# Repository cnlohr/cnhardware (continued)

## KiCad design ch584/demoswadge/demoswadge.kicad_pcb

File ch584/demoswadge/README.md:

# cnlohr's ideal mini swadge

## Goals
 * Swadges have lost their novelty because they're all the same
 * Swadges are too heavy and big.  Smaller. Lighter.
 * Swadges are expensive, what if we make them much cheaper? Can we make more?
 * Keep as much connectivity/features as are visible.  We have to pick and choose.
   * USB ($0.05)
   * Buttons ($0.10)
   * Audio Out ($0.14)
   * Audio In ($0.18)
   * LEDs ($0.35)
   * IMU ($0.55)
   * Compatibility with ESP32-S2 wireless ($1.80)
   * Display ($1.20)
   * Color Display ($2.80)
 * Needs to be more enclosed.

## Spec

 * Single AA Battery, BH-AA-A1AJ020
 * CPU: CH584M (C42381470)
   * 78MHz, RISC-V, IMBC
   * 504kB Flash (Optional +512kB in CH584X)
   * 96kB RAM
   * 2.4GHz (BLE-only, no wifi) support
   * NFC (13.56 MHz RFID)
   * USBFS (Could be USBHS if 585M)
   * 40 GPIOs
   * Processor current is:
     * 5uA Standby (with RTC)
     * 2mA Operating, no radio
     * 7mA (RX)
     * 12mA (Peak TX)
 * Boost supply
   * C5345596, 2.2V VDD, CH584 can run at low voltage.
   * LDO for USB operation to 3.3VDD.
 * OLED or LCD
   * Consider OLED because lower power
   * Consider monochrome OLED for cost (Could 2bit greyscale)
   * Consider LCD but higher power, for color.
 * Silicone Buttons	
 * LEDs (Recommend no LEDs) LC8805C
 * SMALLER PCB (Recommend 35x60)
 * Add a case (not quoted) or triple-stack PCB
 * Recommend no speaker, but headphone jack. Digital volume control.
 * Consider soft-power-switch-only to enable RTC
 * USB (For programmability or other features)

### Costs (@1000)

| Component | Cost | Energy (Active, 100% RX) |
| --- | --- | --- |
| CPU | $0.56 | 7mA |
| Boost x2, LDO | $0.11 | 10-20uA |
| Battery Holder | $0.22 | - |
| LCD/OLED | $2.00-$3.00 | 9-100mA |
| Silicone Buttons | $0.06-$0.35 | - |
| PCB | $0.21-$0.63 | - |
| Misc Discretes | $0.15 | - |
| USB (SOUHAN connector) | $0.05 | - |
| Mic (GMI4013S-2C56DB) | $0.14 | - |
| Headphones PJ-307C | $0.04 | - |
| Crystals (assume internal RTC) | $0.04 | - |
| --- | Optional | --- |
| LEDs 4x | $0.18 | 2mA to 62mA |
| LSM6DS3TR | $0.66 | 450uA (Active mode) |

Silicone button candidates:
 * 
 * 
 * DonGuan Deson Insulated MAterial Co., LTD 10x6x9 Clear, 30k, $0.017/ea

LEDs:
 * LC8805C

PCB:
 * Assumes PCBWay, 35x60, 2L, Lead-free HASL
 * If no case, need 2 extra PCBs to sandwich buttons and OLED/LCD panel.

## Software Recommendations

 * Recommend CH32FUN
 * Recommend compressed loading for game mode.
 * Common funcitons remain in FLASH.
 * Each game has 100% of RAM to itself.
 * Assets **may** stay in FLASH or be loaded into RAM.

## Avenues
 * ESP32-S3 + new screen // AND // Microswadge
 * Micro-swadge only with LCD?

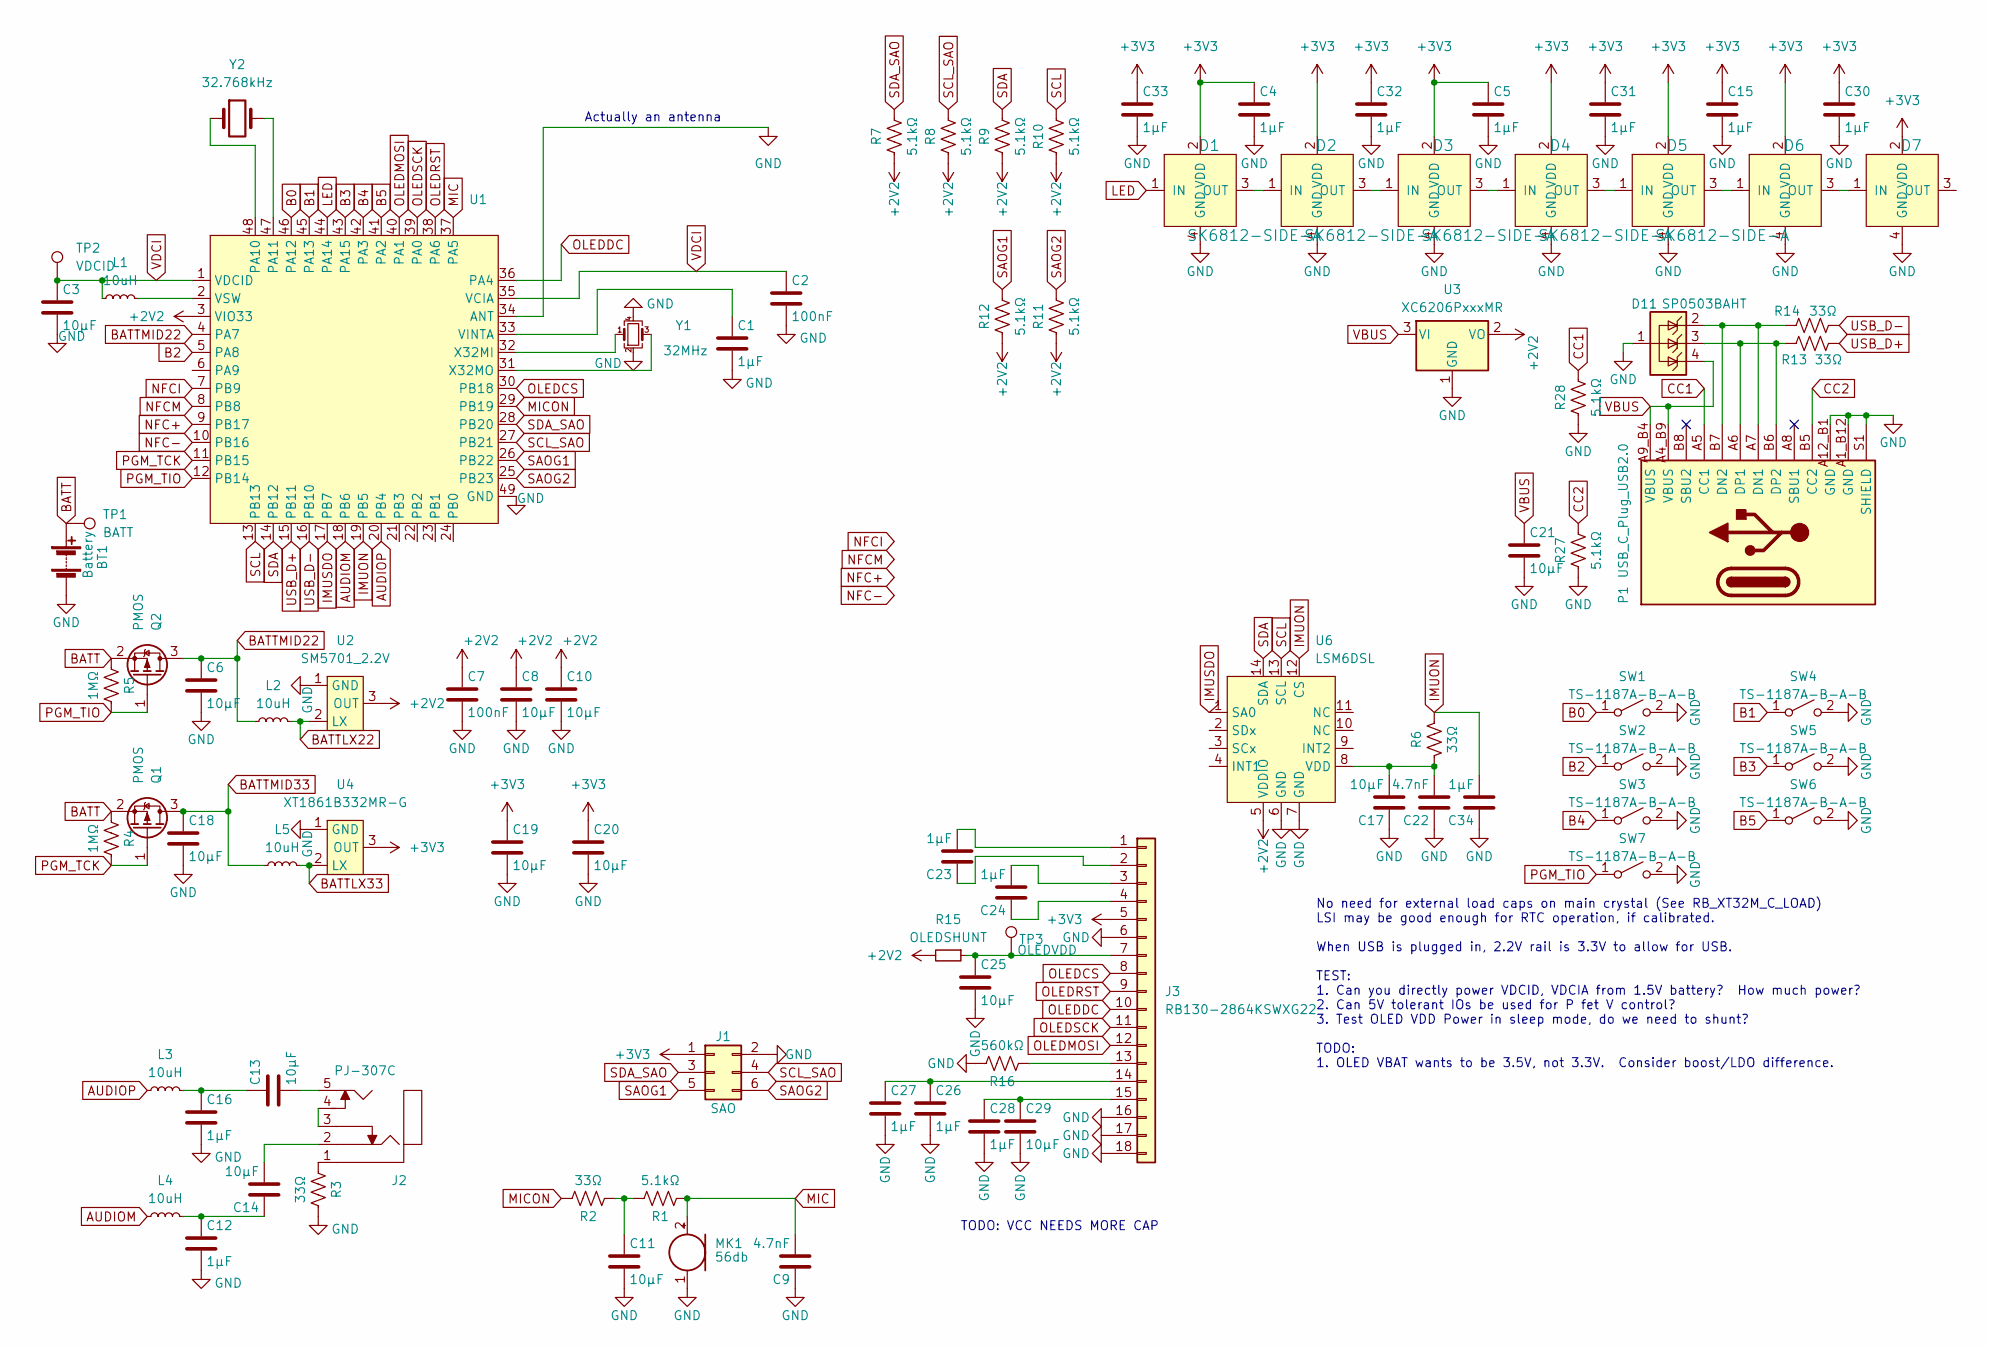
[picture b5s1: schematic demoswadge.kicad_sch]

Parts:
BT1: Battery; 2460; Digikey 36-2460-ND
C1, C4, C5, C12, C15, C16, C23, C24, C26, C27, C28, C30, C31, C32, C33, C34: 1μF; C_0402_1005Metric; LCSC C52923
C2, C7: 100nF; C_0402_1005Metric; LCSC C1525
C3, C6, C8, C10, C11, C13, C14, C17, C18, C19, C20, C21, C25, C29: 10μF; C_0603_1608Metric; LCSC C19702
C9, C22: 4.7nF; R_0402_1005Metric_COMPACT; LCSC C1538
D1, D2, D3, D4, D5, D6, D7: SK6812-SIDE-A; SK6812_SIDE_2; Digikey 1528-4691-ND
D11: SP0503BAHT; SOT-143; Digikey F2715CT-ND
J1: SAO; PinHeader_2x03_P2.54mm_Vertical; LCSC C92272
J2: PJ-307C; LCSC C16684
J3: RB130-2864KSWXG22; FPC-16-P0.50mm-HC-FPC-05-09-16RLTAG-TOP-AND-BOTTOM; LCSC C5213753
L1, L2, L3, L4, L5: 10uH; L_0603_1608Metric; LCSC C307750
MK1: 56db; INGHAi_MIC_GMI4013S-2C58DB; LCSC C529869
P1: USB_C_Plug_USB2.0; USB_C_Receptacle_HRO_TYPE-C-31-M-12; LCSC C2765186
Q1, Q2: PMOS; SOT-23; LCSC C10487
R1, R7, R8, R9, R10, R11, R12, R27, R28: 5.1kΩ; R_0402_1005Metric_COMPACT; LCSC C25905
R2, R3, R6, R13, R14: 33Ω; R_0402_1005Metric_COMPACT; LCSC C25105
R4, R5: 1MΩ; R_0402_1005Metric_COMPACT; LCSC C26083
R15: OLEDSHUNT; R_0402_1005Metric_COMPACT
R16: 560kΩ; R_0402_1005Metric_COMPACT; LCSC C132339
SW1, SW2, SW3, SW4, SW5, SW6, SW7: TS-1187A-B-A-B; BTC007_Button_Silicone
TP1: BATT; TestPoint_Pad_D1.0mm
TP2: VDCID; TestPoint_Pad_D1.0mm
TP3: OLEDVDD; TestPoint_Pad_D1.0mm
U1: QFN-48-1EP_5x5mm_P0.35mm_EP3.7x3.7mm; LCSC C42381470
U2: SM5701_2.2V; SOT-23; LCSC C5345596
U3: XC6206PxxxMR; SOT-23-3; LCSC C5446
U4: XT1861B332MR-G; SOT-23; LCSC C236396
U6: LSM6DSL; LGA-14_3x2.5mm_P0.5mm_LayoutBorder3x4y; LCSC C967633
Y1: 32MHz; Crystal_SMD_2016-4Pin_2.0x1.6mm; LCSC C2965584
Y2: 32.768kHz; Crystal_SMD_3215-2Pin_3.2x1.5mm; LCSC C7294751

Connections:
+2V2: C7.1, C8.1, C10.1, R7.1, R8.1, R9.1, R10.1, R11.1, R12.1, R15.2, U1.3 (VIO33), U2.3 (OUT), U3.2 (VO), U6.5 (VDDIO)
+3V3: C4.1, C5.1, C15.1, C19.1, C20.1, C30.1, C31.1, C32.1, C33.1, D1.2 (VDD), D2.2 (VDD), D3.2 (VDD), D4.2 (VDD), D5.2 (VDD), D6.2 (VDD), D7.2 (VDD), J1.1, J3.5, U4.3 (OUT); also elsewhere on the board
AUDIOM: L4.1, U1.18 (PB6)
AUDIOP: L3.1, U1.20 (PB4)
B0: SW1.1 (A), U1.46 (PA12)
B1: SW4.1 (A), U1.45 (PA13)
B2: SW2.1 (A), U1.5 (PA8)
B3: SW5.1 (A), U1.43 (PA15)
B4: SW3.1 (A), U1.42 (PA3)
B5: SW6.1 (A), U1.41 (PA2)
BATT: BT1.1 (+), Q1.2 (S), Q2.2 (S), R4.1, R5.1, TP1.1
BATTLX22: L2.2, U2.2 (LX)
BATTLX33: L5.2, U4.2 (LX)
BATTMID22: C6.1, L2.1, Q2.3 (D), U1.4 (PA7)
BATTMID33: C18.1, L5.1, Q1.3 (D)
CC1: P1.A5 (CC1), R28.2
CC2: P1.B5 (CC2), R27.2
GND: BT1.2 (-), C1.2, C2.2, C3.2, C4.2, C5.2, C6.2, C7.2, C8.2, C9.1, C10.2, C11.2, C12.2, C15.2, C16.2, C17.1, C18.2, C19.2, C20.2, C21.2, C22.1, C25.2, C26.2, C27.2, C28.2, C29.2, C30.2, C31.2, C32.2, C33.2, C34.1, D1.4 (GND), D2.4 (GND), D3.4 (GND), D4.4 (GND), D5.4 (GND), D6.4 (GND), D7.4 (GND), D11.1 (A), J1.2, J3.6, J3.16, J3.17, J3.18, MK1.1 (-), P1.A1_B12 (GND), P1.A12_B1 (GND), P1.S1 (SHIELD), R3.2, R16.2, R27.1, R28.1, SW1.2 (B), SW2.2 (B), SW3.2 (B), SW4.2 (B), SW5.2 (B), SW6.2 (B), SW7.2 (B), U1.34 (ANT), U1.49 (GND), U2.1 (GND), U3.1 (GND), U4.1 (GND), U6.6 (GND), U6.7 (GND), Y1.2, Y1.4; also elsewhere on the board
IMUON: C34.2, R6.1, U1.19 (PB5), U6.12 (CS)
IMUSDO: U1.17 (PB7), U6.1 (SA0)
LED: D1.1 (IN), U1.44 (PA14)
MIC: C9.2, MK1.2 (+), R1.1, U1.37 (PA5)
MICON: R2.2, U1.29 (PB19)
NFC+: U1.9 (PB17)
NFC-: U1.10 (PB16)
NFCI: U1.7 (PB9)
NFCM: U1.8 (PB8)
unnamed: C11.1, R1.2, R2.1
unnamed: C12.1, C14.1, L4.2
unnamed: C13.1, C16.1, L3.2
unnamed: C13.2, J2.5
unnamed: C14.2, J2.2
unnamed: D1.3 (OUT), D2.1 (IN)
unnamed: D2.3 (OUT), D3.1 (IN)
unnamed: D3.3 (OUT), D4.1 (IN)
unnamed: D4.3 (OUT), D5.1 (IN)
unnamed: D5.3 (OUT), D6.1 (IN)
unnamed: D6.3 (OUT), D7.1 (IN)
unnamed: J2.1, R3.1
unnamed: J2.3, J2.4
unnamed: C23.2, J3.1
unnamed: C23.1, J3.2
unnamed: C24.2, J3.3
unnamed: C24.1, J3.4
unnamed: C25.1, J3.7, R15.1, TP3.1
unnamed: J3.13, R16.1
unnamed: C26.1, C27.1, J3.14
unnamed: C28.1, C29.1, J3.15
unnamed: D11.2 (K), P1.A7 (DN1), P1.B7 (DN2), R14.2
unnamed: D11.3 (K), P1.A6 (DP1), P1.B6 (DP2), R13.2
unnamed: U1.48 (PA10), Y2.1
unnamed: U1.47 (PA11), Y2.2
unnamed: C1.1, U1.33 (VINTA)
unnamed: L1.2, U1.2 (VSW)
unnamed: U1.32 (X32MI), Y1.1
unnamed: U1.31 (X32MO), Y1.3
unnamed: C17.2, C22.2, R6.2, U6.8 (VDD)
OLEDCS: J3.8, U1.30 (PB18)
OLEDDC: J3.10, U1.36 (PA4)
OLEDMOSI: J3.12, U1.40 (PA1)
OLEDRST: J3.9, U1.38 (PA6)
OLEDSCK: J3.11, U1.39 (PA0)
PGM_TCK: Q1.1 (G), R4.2, U1.11 (PB15)
PGM_TIO: Q2.1 (G), R5.2, SW7.1 (A), U1.12 (PB14)
SAOG1: J1.5, R12.2, U1.26 (PB22)
SAOG2: J1.6, R11.2, U1.25 (PB23)
SCL: R10.2, U1.13 (PB13), U6.13 (SCL)
SCL_SAO: J1.4, R8.2, U1.27 (PB21)
SDA: R9.2, U1.14 (PB12), U6.14 (SDA)
SDA_SAO: J1.3, R7.2, U1.28 (PB20)
USB_D+: R13.1, U1.15 (PB11)
USB_D-: R14.1, U1.16 (PB10)
VBUS: C21.1, D11.4 (K), P1.A4_B9 (VBUS), P1.A9_B4 (VBUS), U3.3 (VI)
VDCI: C2.1, C3.1, L1.1, TP2.1, U1.1 (VDCID), U1.35 (VCIA)

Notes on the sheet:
TODO: VCC NEEDS MORE CAP
No need for external load caps on main crystal (See RB_XT32M_C_LOAD) LSI may be good enough for RTC operation, if calibrated. When USB is plugged in, 2.2V rail is 3.3V to allow for USB. TEST: 1. Can you directly power VDCID, VDCIA from 1.5V battery? How much power? 2. Can 5V tolerant IOs be used fo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
Actually an antenna

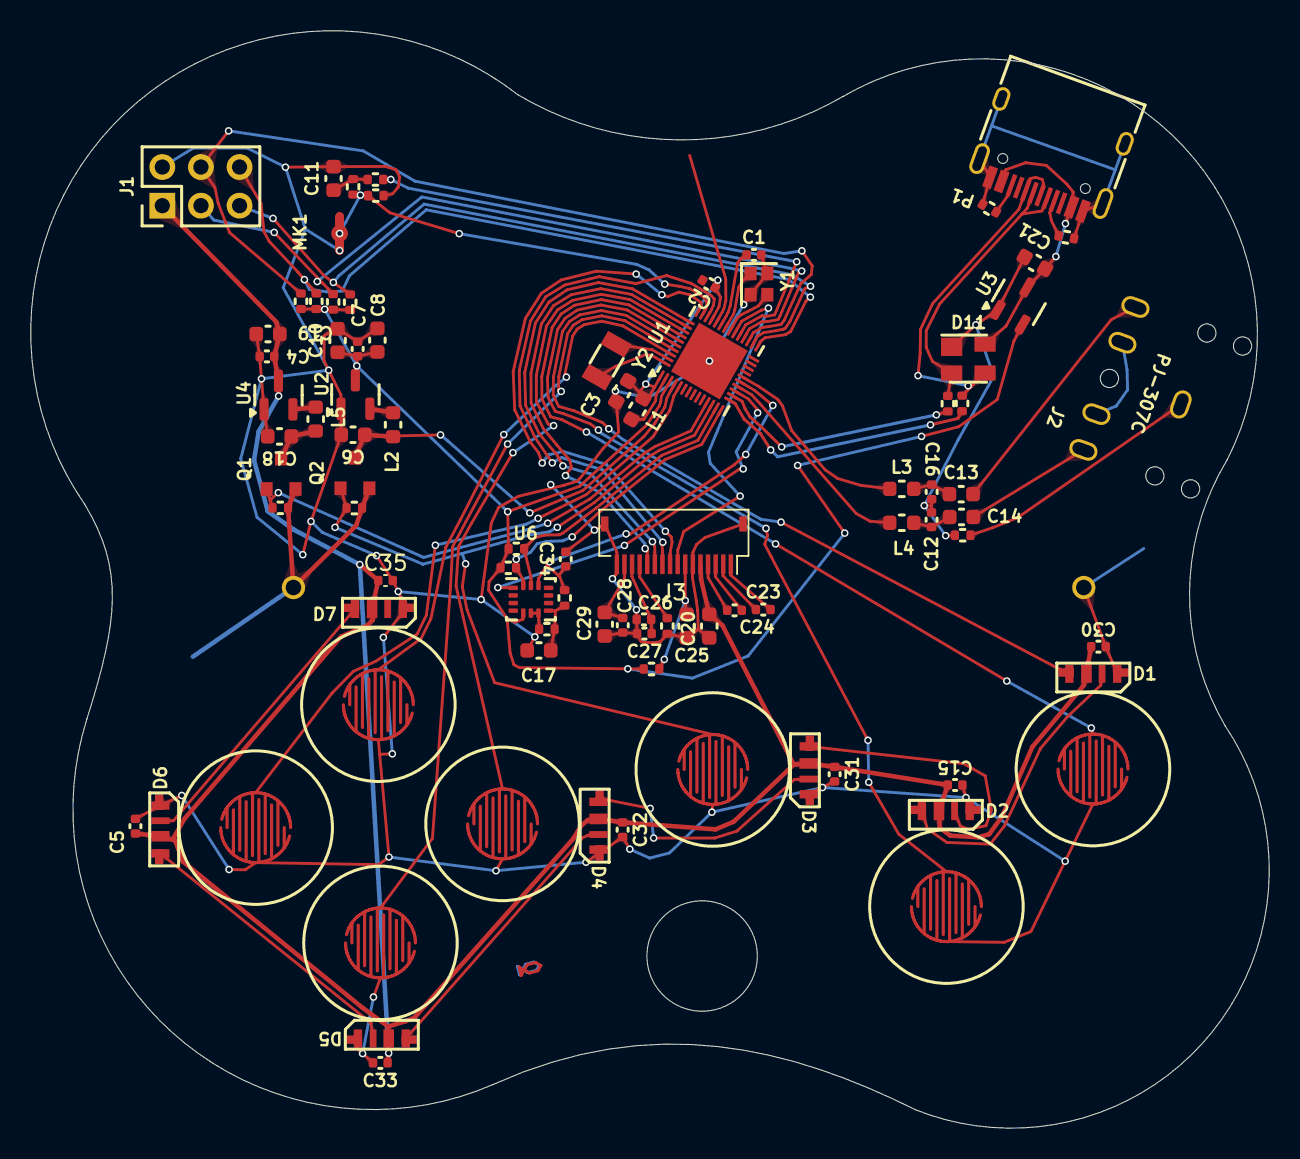
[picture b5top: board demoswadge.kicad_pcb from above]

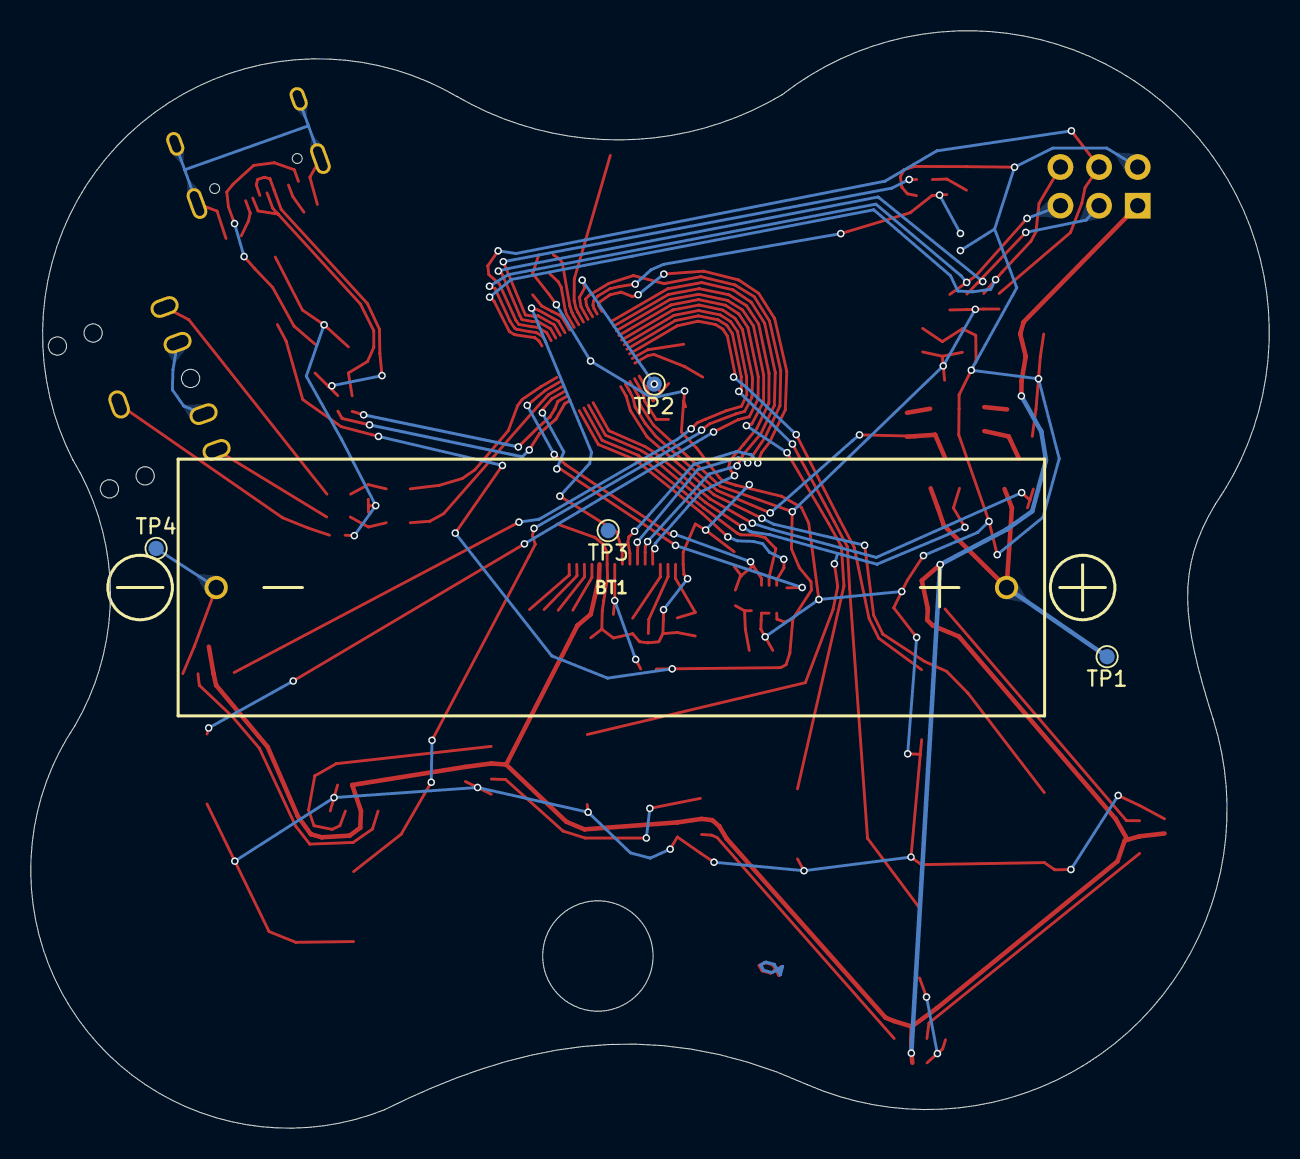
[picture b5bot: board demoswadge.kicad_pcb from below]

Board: 2 copper layers, 81.5 x 72.2 mm, 92 parts (5 on the bottom side), 70 nets.

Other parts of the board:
C35: 1μF; C_0402_1005Metric
TP4: GND; TestPoint_Pad_D1.0mm

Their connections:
+3V3: C35.1; also elsewhere on the board
GND: C35.2, TP4.1; also elsewhere on the board

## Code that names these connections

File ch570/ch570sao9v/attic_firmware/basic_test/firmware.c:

/* Small example showing how to use the SWIO programming pin to 
   do printf through the debug interface */

#include "ch32fun.h"
#include <stdio.h>

#define SH1107_128x128

#define SSD1306_RST_PIN  PA6
#define SSD1306_CS_PIN   PA4
#define SSD1306_DC_PIN   PA10
#define SSD1306_MOSI_PIN PA7
#define SSD1306_SCK_PIN  PA5

//#define SSD1306_SOFT_SPI 1

#include "ssd1306_spi.h"
#include "ssd1306.h"

uint32_t count;





/////////////////////////////////////////////////////////////////////////////////////////////////
/////////////////////////////////////////////////////////////////////////////////////////////////
// FakeDC
//
// Fake digital-to-analog, by looking at the time constant on a capcaitor
// and waiting for the scmitt trigger flip.
//

#define CAPACITANCE 0.00000001
#define RESISTANCE  33000.0
#define VREF 1.75
#define FIXEDPOINT_SCALE 100

volatile uint32_t lastfifo = 0;

void TMR1_IRQHandler(void) __attribute__((interrupt))  __attribute__((section(".srodata")));
void TMR1_IRQHandler(void)
{
	R8_TMR_INT_FLAG = 2;
	lastfifo = R32_TMR_FIFO;
	funPinMode( PA2, GPIO_ModeOut_PP_20mA );
}


// The timing on the setup has to be tight.
void EventRelease(void) __attribute__((section(".srodata"))) __attribute__((noinline));
void EventRelease(void)
{
	R8_TMR_CTRL_MOD = 0b00000010; // Reset Timer
	R8_TMR_CTRL_MOD = 0b11000101; // Capture mode rising edge
	funPinMode( PA2, GPIO_ModeIN_Floating );
}

void SetupADC(void)
{
	R8_TMR_CTRL_MOD = 0b00000010; // All clear
	R32_TMR_CNT_END = 0x03FFFFFF; // Maximum possible counter size.
	R8_TMR_CTRL_MOD = 0b11000101; // Capture mode rising edge
	R8_TMR_INTER_EN = 0b10; // Capture event.

	R16_PIN_ALTERNATE_H |= 1<<6; // Map PA2 to CAP1 (could be PA7, PA4, or PA9) (see RB_TMR_PIN)

	NVIC_EnableIRQ(TMR1_IRQn);
	__enable_irq();

	funPinMode( PA2, GPIO_ModeOut_PP_20mA );
}

/////////////////////////////////////////////////////////////////////////////////////////////////















int main()
{
	SystemInit();

	funGpioInitAll(); // no-op on ch5xx

	funPinMode( PA11, GPIO_CFGLR_OUT_10Mhz_PP );
//	funDigitalWrite( PA11, 1 ); // BS1 = 1 for I2C
	funDigitalWrite( PA11, 0 ); // BS1 = 0 for SPI

	funPinMode( PA6, GPIO_CFGLR_OUT_10Mhz_PP );
	funDigitalWrite( PA6, 1 ); // RES
	funPinMode( PA4, GPIO_CFGLR_OUT_10Mhz_PP );
	funDigitalWrite( PA4, 0 ); // SCS
	funPinMode( PA10, GPIO_CFGLR_OUT_10Mhz_PP );
	funDigitalWrite( PA10, 0 ); // D/C



	ssd1306_rst();
	ssd1306_spi_init();
	ssd1306_init();
	ssd1306_setbuf(0x00);

	// Turbo-time
	ssd1306_cmd(0xD5);
	ssd1306_cmd(0xe0);


	ssd1306_cmd(0xc8);
	ssd1306_cmd(0xa1);


	SetupADC();

	int frameno = 0;

	int debug = 0;

	unsigned start;

	while(1)
	{

		start = SysTick->CNT;

		uint32_t pressures[4];

		int btn = 0;
		for( btn = 0; btn < 4; btn++ )
		{
			// try GPIO_CFGLR_IN_PUPD, GPIO_ModeIN_Floating, GPIO_CFGLR_OUT_10Mhz_PP as well
			funPinMode( PA3, GPIO_ModeIN_Floating );
			funPinMode( PA8, GPIO_ModeIN_Floating );
			funPinMode( PA9, GPIO_ModeIN_Floating );
			switch( btn )
			{
			case 0:
				funPinMode( PA8, GPIO_CFGLR_OUT_10Mhz_PP );
				funDigitalWrite( PA3, 1 );
				break;
			case 1:
				funPinMode( PA9, GPIO_CFGLR_OUT_10Mhz_PP );
				funDigitalWrite( PA8, 1 );
				break;
			case 2:
				funPinMode( PA3, GPIO_CFGLR_OUT_10Mhz_PP );
				funDigitalWrite( PA9, 1 );
				break;
			}


			lastfifo = 0;
			EventRelease();
			int to = 4000;
			while( !lastfifo && --to );

			#define COEFFICIENT (const uint32_t)(FUNCONF_SYSTEM_CORE_CLOCK*(RESISTANCE*CAPACITANCE)*VREF*FIXEDPOINT_SCALE+0.5)
			int r = lastfifo - 2; // 2 cycles back.
			int vtot = COEFFICIENT/r + ((const uint32_t)(VREF*FIXEDPOINT_SCALE));
			pressures[btn] = vtot - 70;
		}
		debug = SysTick->CNT - start;
		frameno++;
		
		ssd1306_setbuf(0x00);

		char st[128];
		sprintf( st, "%08x", (int)SysTick->CNT );
		ssd1306_drawstr_sz(0, 0, st, 1, 2 );

		sprintf( st, "%3d %d", debug>>8, (int)pressures[3] );
		ssd1306_drawstr_sz(0, 24, st, 1, 2 );


		for( btn = 0; btn < 3; btn++ )
		{
			int x = 32 + btn * 32;
			int y = 90;
			int p = pressures[btn]>>9;
			//ssd1306_drawCircle( x, y, 
			ssd1306_fillCircle( x, y, p, 1 );
		}


		ssd1306_refresh();
	}
}

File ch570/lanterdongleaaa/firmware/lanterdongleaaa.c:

/* 
	In progress.  Trying to jank an ADC out of a ch57x.

	// Mic (with pull-up) on pa3
	// RC on PC7->PC2
*/


#include "ch32fun.h"
#include <stdio.h>

#include "ch5xx_lowpower.h"
#include "color_utilities.h"

#ifdef CH570_CH572
#define LED PA9
#else
#define LED PA8
#endif


#define USE_UART_OUT

uint32_t count;
int initialSWD;
int frameno = 18;

int last = 0;
void handle_debug_input( int numbytes, uint8_t * data )
{
	last = data[0];
	count += numbytes;
}

uint32_t timer_data[256];


void RunFunction() __HIGH_CODE;

void OutputLEDs( uint32_t * ledcolors )
{
	int led;
	for( led = 0; led < 6; led++ )
	{
		uint32_t color = ledcolors[led];
		for( int cb = 0; cb < 24; cb += 1 )
		{
			// USART is - I think? LSB first?
			// LOW (start) / x x H L x x H H H(stop?)
			uint8_t pair = ((color >> (23-cb))&1);
			//const uint8_t sendc[4] = { 0b00001000, 0b00001111, 0b11101000, 0b11101111, };
			//const uint8_t sendc[2] = { 0b10000000, 0b11111110 };
			//while(!(R8_UART1_LSR & RB_LSR_TX_ALL_EMP));
			//Delay_Us(1);
			if( pair )
			{
				funDigitalWrite( PA1, 1 );
				ADD_N_NOPS(40);
				funDigitalWrite( PA1, 0 );
				ADD_N_NOPS(12);
			}
			else
			{
				funDigitalWrite( PA1, 1 );
				ADD_N_NOPS(12);
				funDigitalWrite( PA1, 0 );
				ADD_N_NOPS(40);
			}
			//R8_UART1_THR = sendc[pair];
		}
	}
}

#define PWMCLOCKDIV 4
#define INITIAL_ZERO 128
// SPS = F_CPU/(PWMCLOCKDIV*255*oversample)

// Highest quality combination so far - 100MHz / (1 oversample*5clockdiv*255) = 78.431kSPS
// Good quality combination so far - 75MHz / (1 oversample*5clockdiv*255) = 78.824kSPS
// Actually amazing: 100MHz / (1 oversample*4clockdiv*255) = 98.039kSPS

void RunFunction()
{

	const uint32_t oversample = 4;
	const uint32_t targetsampletime = oversample*(255*R16_PWM_CLOCK_DIV); // in 1/60Mths of a second.

	uint32_t * rptr = timer_data;
	uint32_t * end = &timer_data[sizeof(timer_data)/sizeof(timer_data[0])];
	uint32_t place = 0;
	int32_t rvalue = 0;

	int remote_estimate = 0;

	int accumulated_dc = 0;

	LSIEnable(); // Disable LSE, enable LSI
	RTC_init();

	// LED Test
#if 0
	R16_PIN_ALTERNATE &= ~RB_PIN_DEBUG_EN;

	//while(1)
	int i;
	for( i = 0; i < 10; i++ )
	{
		#define NR_LEDS 6
		static uint32_t ledcolors[NR_LEDS] = { 0x00ff00, 0x0000ff, 0x00ff00, 0x00ff00, 0xff00ff, 0x00ffff };

		static uint16_t phases[NR_LEDS];


		for( int k = 0; k < NR_LEDS; k++ )
		{
			phases[k] += ((((rands[k&0xff])+0xf)<<2) + (((rands[k&0xff])+0xf)<<1))>>1;
		}


		funDigitalWrite( PA1, 0 );
		funPinMode(PA1, GPIO_CFGLR_IN_PUPD );
		Delay_Ms(3);
		funPinMode(PA1, GPIO_CFGLR_OUT_50Mhz_PP); //LED Out / Buttons in
		Delay_Us(50);

		volatile int tween = -NR_LEDS;

		int ledno;
		for( ledno = 0; ledno < NR_LEDS; ledno++ )
		{
			uint8_t index = (phases[ledno])>>8;
			uint8_t rsbase = sintable[index];
			uint8_t rs = rsbase>>3;
			uint32_t fire = ((huetable[(rs+190)&0xff]>>1)<<0) | ((huetable[(rs+30)&0xff])<<8) | ((huetable[(rs+0)]>>1)<<16);

			uint32_t rgbuke  = ((huetable[(frameno+170+ledno*40)&0xff]>>1)<<0) | ((huetable[(frameno+85+ledno*40)&0xff]>>1)<<8) | ((huetable[(frameno+0+ledno*40)&0xff]>>1)<<16);

			// Because this chip doesn't natively support multiplies, we are going to avoid tweening of 1..254.
			//return TweenHexColors( fire, ice, ((tween + ledno)>0)?255:0 ); // Where "tween" is a value from 0 ... 255
			ledcolors[ledno] = rgbuke;

		}

		OutputLEDs(ledcolors);

		int i;
		for( i = 0; i < 8; i++ )
		{
			Delay_Ms(1);
			//LowPowerIdle( MS_TO_RTC(1) );
			//DCDCEnable(); // During low power mode, the DCDC is disabled so we need to enable it

			if( initialSWD != funDigitalRead( PA0 ) )
			{
				R16_PIN_ALTERNATE |= RB_PIN_DEBUG_EN;
			}
		}
		frameno++;
	}
	R16_PIN_ALTERNATE |= RB_PIN_DEBUG_EN;

#endif

	while(1)
	{
		uint32_t * cnow = (void*) (R16_TMR_DMA_NOW | (((intptr_t)timer_data)&0xffff0000));
		if( cnow == end ) cnow = end - 1;
		while( rptr != cnow )
		{
			uint32_t v = *(rptr++);

			// For each edge.
			int negative = 0;
			if( v & 0x02000000 )
			{
				v = v & 0x1ffffff;
				negative = 1;
			}

			int tprog = v;

//			place += v;

			do
			{
				int leftover = place + tprog - targetsampletime;

				if( leftover > 0 )
				{
					// We bridge over.  Need to see how much data was left.
					int fillcur = targetsampletime - place;
					place += fillcur;
					tprog -= fillcur;
					if( negative )
						rvalue -= fillcur;
					else
						rvalue += fillcur;					
				}
				else
				{
					// No leftover.  Add remaining part.
					place += tprog;
					if( negative )
						rvalue -= tprog;
					else
						rvalue += tprog;
					break;
				}

//rvalue is always divisible by 2.
rvalue>>=1;

static int ifp, rvmin, rvmax;
ifp++;

if( ifp == 1000 )
{
	printf( "%d %d %d\n", rvalue, R8_PWM1_DATA, rvmax-rvmin );
	//printf( "." );
	rvmin = 100000;
	rvmax = -100000;
	ifp = 0;
}
else
{
	if( rvalue < rvmin ) rvmin = rvalue;
	if( rvalue > rvmax ) rvmax = rvalue;
}

				//audio_samples[audiosamphead] = rvalue;
				//audiosamphead = (audiosamphead + 1) % ASAMPS;
#if 0
				int err = (rvalue>>2) - remote_estimate;
				int value = 0;

				if( err > 127 ) err = 127;
				if( err < -127 ) err = -127;
				value = err;

#if 0
	static int ak;
				ak++;
				value = ak;
#endif
				printf( "%d\n", value );
				remote_estimate += err;

#endif


				accumulated_dc += rvalue;
				rvalue = 0;

				place -= targetsampletime;
			} while(1);



			if( rptr == end ) rptr = timer_data;
		}


		//printf( "%08x\n", R16_TMR_DMA_NOW );
		// Should print 00001310 020000a0 00001310 020000a0
//		printf( "%08x %08x %08x %08x @ %08x\n", (int)timer_data[0], (int)timer_data[1], (int)timer_data[2], (int)timer_data[3], R16_TMR_DMA_NOW );
		//printf( "%6d %5d %d\n", audio_samples[audiosamphead], place, audiosamphead );
	//	printf( "%x\n",  audio_samples[(audiosamphead-1+ASAMPS)&(ASAMPS-1)]+32767 );
		//printf( "." );
	//	_write( 0, "12345", 5 );




		// Steps disrupt the sampling. Minimize how often we do it.
		if( accumulated_dc > 10000000 && R8_PWM1_DATA > 0 ) { R8_PWM1_DATA++; accumulated_dc = 0; }
		if( accumulated_dc <-10000000 && R8_PWM1_DATA < 254 ) { R8_PWM1_DATA--; accumulated_dc = 0; }
		accumulated_dc = accumulated_dc - (accumulated_dc>>23);

		//if( R8_PWM1_DATA++ > 28 ) R8_PWM1_DATA = 1;
	}
}

int main()
{
	SystemInit();

	funGpioInitAll(); // no-op on ch5xx

	// Pull-up PA3
//	R32_PA_PU |= 0b1100; // Extra pull-up on mic - why?
//	R32_PA_PD_DRV |= 0b0100;
	// doesn't do anything?

	// UART Config
//	SetupUART(FUNCONF_UART_PRINTF_BAUD); // UART1 on rx,tx:PA8,PA9 at 115200 baud (PA2,PA3 on ch570/2)

	//Not using UART: TXD_7: TXD pin mapping of UART.
	funPinMode(PA1, GPIO_CFGLR_OUT_50Mhz_PP); //LED Out

	funPinMode(PA7, GPIO_CFGLR_OUT_2Mhz_PP); //PWM1

	// Comparator mapping default.
	funPinMode(PA2, GPIO_CFGLR_IN_FLOAT); // PA2 is Microphone
	funPinMode(PA3, GPIO_CFGLR_IN_FLOAT); // PA3 is Sawtooth in.

	// Slight pull SWIO high.
	funDigitalWrite(PA0, 1); 
	funPinMode(PA0, GPIO_CFGLR_IN_PUPD ); 

	// TODO: Explore this. TODO Explore.
	SYS_SAFE_ACCESS(
		R16_AUX_POWER_ADJ = 1;
		R16_POWER_PLAN = RB_PWR_PLAN_EN | RB_PWR_SYS_EN | RB_PWR_RAM2K | RB_PWR_CORE;
	);

	SYS_SAFE_ACCESS(
		R16_POWER_PLAN |= RB_PWR_DCDC_EN; // Enable core DC DC
	);

	Delay_Ms(100);

	SYS_SAFE_ACCESS( 
		R16_PIN_ALTERNATE = 
			RB_PIN_DEBUG_EN | // Disable to disable debug.
			0b111101111100; // Low power unused pins.
		R16_PIN_ALTERNATE_H = 0; // All default mapping.
	);

	initialSWD = funDigitalRead( PA0 );

	// Configure comparator to output to timer capture.
	R32_CMP_CTRL = 
		(0<<25) | // RB_APR_OUT_CMP = realtime output. -- what does this even do?
		(0) |     // RB_CMP_SW = 0 = PA2/PA3.
		(1<<1) |  // RB_CMP_CAP = 1: Input comes from the comparator;
		(1<<0);   // RB_CMP_EN = 1.

	// Setup 26-bit capture timer - default on PA7.
	R8_TMR_CTRL_MOD = 
		(0b01<<6) | // RB_TMR_CAP_EDGE = Capture the time between any edge changes;
		0 |         // RB_TMR_CAP_COUNT = Capture mode.
		(1<<2) | 	// RB_TMR_COUNT_EN = 1
		(1<<1) |	// RB_TMR_ALL_CLEAR = 1
		(1<<0); 	// RB_TMR_MODE_IN = 1 (Input mode)
	R8_TMR_CTRL_MOD &= ~(1<<1); // Clear R8_TMR_CTRL_MOD.
	R16_TMR_DMA_BEG = (uintptr_t)&timer_data[0];
	R16_TMR_DMA_END = (uintptr_t)&timer_data[sizeof(timer_data)/sizeof(timer_data[0])]; // END is not inclusive.

	R8_TMR_CTRL_DMA =
		(1<<2) | // RB_TMR_DMA_LOOP
		(1<<0);  // RB_TMR_DMA_ENABLE


	// Base is 952.4 @ 5-bit (31 period) = 60MHz base clock.
	// Or 100MHz...
	R16_PWM_CLOCK_DIV = PWMCLOCKDIV;
    R8_PWM_OUT_EN |= (1 << (0)); // Enable output 0.
    R8_PWM_CONFIG &= ~(RB_PWM_CYC_MOD | RB_PWM_CYCLE_SEL);
    R8_PWM_CONFIG |= 0 << 2; // 0 = 8-bit, 3 << 2 = 5-bit (??? why not?), 2 << 2 = 6-bit, 1 << 2 = 7-bit.
    R8_PWM_CONFIG |= RB_PWM_CYCLE_SEL;
	R8_PWM1_DATA = INITIAL_ZERO; // Adjust 0 offset.


	RunFunction();

}
